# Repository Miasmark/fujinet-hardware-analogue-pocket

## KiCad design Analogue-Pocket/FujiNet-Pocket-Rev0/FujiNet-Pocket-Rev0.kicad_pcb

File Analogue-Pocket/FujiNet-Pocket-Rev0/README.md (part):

# FujiNet Pocket Rev0 (draft)

A **FujiNet for the Analogue Pocket's cartridge slot**. On the Pocket the FPGA core is the
cartridge:
- It serves the console's FujiNet mailbox to the running program.
- It sends each request as a FujiBus packet in a SLIP frame at 115,200 baud 8N1, on cartridge
  pin 5, and listens on pin 31.

This board is therefore only the FujiNet half of a FujiNet cartridge: no bus logic, no SRAM, no
console-side microcontroller. It is the same for every Pocket core that speaks this link. The
first is openFPGA-7800 (2.2.7: CONFIG, the network devices and game loading, tested with
fujinet-pc on the link port). An Intellivision core and a 2600 core are scoped to follow.
Cores of the cart's own, a net terminal and a text web browser, are scoped in
[docs/NET_CORES_SCOPING.md](docs/NET_CORES_SCOPING.md).

**Status (2026-11-20): draft, schematic and board.** It is placed and routed, but has not
been ordered, built or run, and has not been fitted to a Pocket.

| Check | Result |
|---|---|
| ERC (all severities) | 0 errors, 0 warnings |
| Netlist parity (kicad-cli netlist vs `tools/design.py`) | 41 / 41 nets |
| `tools/check_pins.py` (the netlist vs `firmware/pocket.h`, plus the link path) | pass |
| DRC, errors, with schematic parity | 0 violations, 0 unconnected, 0 parity |
| DRC warnings | 4: 2 dangling stitch vias, 2 silk near the edge |
| Shell, fit in a Pocket | draft shell drawn (`case/`), not yet printed or fitted |

`tools/build_all.sh` regenerates the schematic and the checks; `LAYOUT=1 tools/build_all.sh`
also regenerates the board and its outputs. It needs:
- KiCad 10 and Python 3;
- for the board, KiCad's pcbnew Python module (`PCBNEW_PYTHON`, default `/usr/bin/python3`) and
  numpy;
- Freerouting 2.4.1, which needs Java 25 (`JAVA` names the binary).
- The circuit lives in `tools/design.py`.
- The sheet drawings live in `tools/sch_layout.py`.
- The `.kicad_sch` files are output: edit the Python, not them.
- The generator, the drawing toolkit and its checks are FujiNet-7800-Rev0's (`ATARI-7800/`).

## Block diagram

```
Pocket slot ──pin 5──100R──[LVC1G34 on +3V3]──────── UART1 RX (IO17) ┐
            ──pin 31─100R──[LVC1G34 on CART_VCC]──── UART1 TX (IO18) ├ ESP32-S3-WROOM-1-N16R8 ── microSD
            ──pin 1 (CART_VCC) ─┐                                    │   UART0 ── CP2102N ── USB-C
                                └─ BAT54C ─ PWR_EN ─ TPS63001 (3.3 V)┘                         │
                                     VBUS ─┘           ▲ VSYS                                  │
                         LiPo ── AO3401A ──────────────┤                                       │
                          ▲                 SS34 ──────┘◄────────────── VBUS ◄────────────────┘
                          └── MCP73831 (4.20 V, 213 mA) ◄── VBUS
```

## The slot side (sheet 2)

The Pocket's slot is a GB / GBA edge: 32 fingers at 1.5 mm on one face.

| Pin | GBA / GB name | Net | Use |
|---|---|---|---|
| 1 | VCC | CART_VCC | The cart rail: 3.3 V while the Pocket runs with cart power on. The core asks for it (`core.json` `cartridge_adapter` 0). |
| 5 | /CS | POCKET_TX | The core's TX, idle high. |
| 31 | /REQ (GB: VIN) | POCKET_RX | The core's RX. |
| 32 | GND | GND | |
| others | | open | Analogue's template leaves them as they are: bank 0 an output held high, the rest inputs. |

- **Two SN74LVC1G34 buffers, both with Ioff** (partial power-down), so neither side ever feeds the
  other when it is off:
  - **RX buffer:** runs on the device's +3V3.
  - **TX buffer:** runs on the Pocket's own rail (pin 1).
  - The Pocket can be on with the device's cell flat, and the device can be on (charging, flashing)
  with the Pocket off.
- **100R in series at each finger.**
- **100k pull-downs** hold an unpowered side's line low:
  - The core counts a line only once it has idled high for 1 ms, so a low pin 31 is never heard.
  - The S3 sees a break, not noise.
- **Pin 1 also feeds the enable diode:** about 30 uA.

**Edge geometry** (`tools/make_edge_fp.py`) is re-drawn from Gekkio's GB-CART32K-A (gb-hardware,
CC-BY-4.0):
- pins 2-31 are 1.0 x 5.5 mm;
- pins 1 and 32 are 1.3 x 6.0 mm, so the rail and ground make contact first;
- the tab is 49.2 x 8.6 mm;
- the board is 1.0 mm thick.

**To verify on a Pocket before ordering boards:** which face the fingers are on, and pin 1.

## The FujiNet half (sheets 3 and 4)

FujiNet-7800-Rev0's circuits, unchanged except as noted:
- **ESP32-S3-WROOM-1-N16R8:** with its EN RC, S3_RST and S3_BOOT buttons, and 22 uF bulk.
- **microSD:** TF-015, SPI, with pull-ups.
- **USB-C:** HRO TYPE-C-31-M-12, 5.1k Rd, ESD.
- **CP2102N:** on UART0, with the UMH3N esptool auto-program pair.

Changed:
- **The link:** UART1 on IO17 (RX) and IO18 (TX) replaces the RP2354B's native USB and its
  RUN / BOOTSEL lines.
- **Status LEDs:** two plain LEDs, active low from +3V3, replace the WS2812C, which needs 3.7 V
  or more; this board has no 5 V rail.
  - WiFi: green, IO14.
  - Bus: red, IO16.

## Power (sheet 5)

The device powers itself. The Pocket's cart rail has only been seen to supply about 0.2 W. An
ESP32-S3 on WiFi averages more than that and peaks several times higher (openFPGA-7800
`docs/FUJINET_POCKET_DEVICE.md`, section 5).

- **Cell:** a protected 1S LiPo pouch up to 30 x 50 x 5 mm, for example a 403050 or 503050
  (about 600-1000 mAh). It rides over the components on a shelf in the shell (layout below), with
  its leads soldered to two pads on the board, marked + and -. There is no connector, so there is
  no JST-PH polarity to get wrong.
  - The board has no protection circuit of its own: the cell's is relied on.
  - The cell is bought separately and is not on the BOM.
- **Charger:** MCP73831-2 (4.20 V), 213 mA (R_PROG 4.7k, about 0.5 C for 400 mAh), from USB
  only, with a charge LED.
- **Power path** (Microchip AN1149, as the 7800 board's 5 V OR):
  - USB VBUS goes through an SS34 onto VSYS.
  - The cell goes through an AO3401A, gate on VBUS: on without USB, off with it, so USB runs the
    board while the cell charges.
  - 4.7k holds the gate down against the SS34's leakage.
- **3.3 V:** a TPS63001 buck-boost, 1.8-5.5 V in. It holds 3.3 V over the cell's whole 3.0-4.2 V
  and through WiFi bursts.
  - PS/SYNC is tied low: power-save mode at light load.
- **Enable:** `PWR_EN = CART_VCC or VBUS` (BAT54C, 100k down).
  - The board runs while the Pocket is on, or while USB is in (charging, flashing).
  - Otherwise the regulator is shut down: no power switch is needed.

## Firmware

`firmware/pocket.h` and `firmware/platformio-fujinet-pocket.ini` are proposed for fujinet-firmware
as `include/pinmap/pocket.h` and `build-platforms/platformio-fujinet-pocket.ini`:
- **The build:** the generic RS232 build (`BUILD_RS232`) on a wired UART, as `rs232_s3.h`.
- **Pin assignments:**
  - **UART1:** the link, on 17 and 18. Defining `PIN_UART1_RX` is what selects the wired UART in
    `lib/bus/rs232/rs232.h`.
  - **SD and UART0:** as `fujiversal-rs232.h`.
  - **LEDs:** on 14 and 16.
  - **Not used:** the modem control lines and keys.cpp's buttons are `GPIO_NUM_NC`.
    `common.h` would otherwise put button C on GPIO14, this board's WiFi LED.

`pinmap.h` also needs its `#include "pinmap/pocket.h"`. Neither file has been compiled yet.

**It is also a modem.** The stock RS232 firmware passes any bytes outside
FujiBus frames to FujiNet's Hayes-style modem: a terminal core on the cart's
pins (NetTerm, Mode FujiNet Modem) dials Telnet BBSs with `ATDT host:port`.
See `docs/NET_CORES_SCOPING.md`, section 2.
## The board

- **Size and stack:** 51.4 x 82 mm, 1.0 mm thick, 4 layers:
  - F.Cu: signals and a GND pour;
  - In1: GND plane;
  - In2: +3V3 plane;
  - B.Cu: signals and a GND pour.
- **The tab:** the GB / GBA tab with its 32 fingers. The insertion corners are 0.9 mm arcs, as a
  GB cartridge's.
- **The voltage-switch corner:** on the left (pin 1's side, seen from the component side with
  the fingers down), the tab's edge runs straight on up 10 mm past the tab base before the body
  steps out to full width. The shell's GBA-shaped corner there then clears the Pocket's voltage
  switch. The height is an **estimate** (`gen_pcb.NOTCH_H`).
- **The Pocket's cartridge recess** (estimates, both drawn on the board's Fab layers):
  - **Back:** below about 31 mm from the insertion edge, the board's flat back lies nearly flush
    against the Pocket. Nothing is placed on the back.
  - **Front** (the component side, the fingers' side): it faces the recess's open side, covered
    only by the Pocket's lip below about 15 mm from the insertion edge. Only low parts go there:
    the two link buffers over pins 5 and 31, the bring-up pads, the cell's lead pads.
- **Above the recess, on the front:**
  - the ESP32-S3 at the top, its antenna flush with the top edge over its keep-out band (no
    copper, holes or parts across the board there);
  - USB-C on the west side and microSD on the east side;
  - the reset and BOOT buttons and the three LEDs down the west side;
  - below the module: the charger and power path, the TPS63001, the CP2102N.
- **The battery, on a shelf in the shell:**
  - the cell lies over the components, on a shelf whose top face is 4.4 mm above the board. The
    tallest parts under it are the module and USB-C, at 3.1-3.2 mm.
  - its place, 30 x 50 mm (x 88..118, y 79..129), is drawn on F.Fab and in the shell anchors. It
    is clear of the antenna band and the two buttons.
  - its leads come down from its lower end to two pads on the component side, just above the lip:
    `+` at the east, `-` at the west.
  - the 3D export shows a 30 x 50 x 4 mm stand-in at that height.
  - nothing is placed on the back, so assembly is single-sided.
- **Six M2 holes** (2.2 mm) for the shell, each kept 3 mm clear of parts:
  - two by the top corners, below the antenna band;
  - two just above the slot line;
  - two inside the slot.

  `case/board-anchors.json` and `.scad` carry them for the shell design, with the outline, the
  ports, buttons, LEDs and the cell. `case/README.md` lists what the shell must respect: the
  GBA-shaped corner, the antenna, the openings and the cell's room to swell.
- **Routing:** generated, as for FujiNet-7800-Rev0. The order:
  1. `tools/gen_pcb.py` places the parts from `tools/placement.py` and fans out the planes. It also
     lays four things down by hand, locked:
     - the TPS63001's pins, to its inductor and capacitors as its datasheet shows, and its VIN /
       VINA loop;
     - the USB pair: the USB-C crossover (D- under it on B.Cu, through two 0.45 / 0.2 mm vias),
       on to the ESD diodes, then on B.Cu under the SS34 and the power path to the CP2102N's
       pins 4 and 5;
     - the UART0 escapes from the module to B.Cu;
     - the GND finger's stub.
  2. Freerouting routes the rest.
  3. The 7800 board's finisher closes what is left; stitching vias tie the GND pours to In1.
- **Outputs** (`tools/export_fab.py`): `exports/`
  - gerbers and drill;
  - the front position file;
  - `FujiNet-Pocket-Rev0.step` (the board with every model and the cell's stand-in, for the
    shell);
  - the renders in `docs/`.

## Measure with the breakout cart

These numbers are estimates in the board and shell; each is one setting in `tools/gen_pcb.py`
(and `tools/placement.py` for the slot line), then `LAYOUT=1 tools/build_all.sh` re-runs the
layout and the shell anchors.

| # | Measure | Now (estimate) | Setting |
|---|---|---|---|
| 1 | **Voltage switch:** how far above the tab base the left corner must stay at the tab's width | 10 mm | `NOTCH_H` |
| 2 | **Seated depth:** how far from the insertion edge the board's back starts lying against the Pocket | 31 mm (y = 119) | `SLOT_Y` (gen_pcb.py and placement.py) |
| 3 | **Lip:** how far up the component side the Pocket's lip covers (low parts only below) | 15 mm (y = 135) | `LIP_Y` (gen_pcb.py and placement.py) |
| 4 | **Board thickness** the slot wants | 1.0 mm (Gekkio's GB boards) | `THICKNESS` |
| 5 | **Pin 1 side:** VCC (pin 1) on the left, seen from the contact side with the fingers down | as Gekkio's footprint | `make_edge_fp.py` |

**Final pass, after the measurements and the re-route:** clear the DRC warnings left then.
Today these are 2 dangling stitching vias and 2 silkscreen texts near the edge. Re-check the
renders and the shell anchors, and fit a printed blank.

## Before ordering boards

1. **Edge:** check the finger face, pin 1 and the board thickness (1.0 mm, as Gekkio's GB
   boards) against a GB cartridge in a Pocket. Measure where the Pocket's shell top falls on the
   board (31 mm from the insertion edge is assumed), and how far up the component side the
   Pocket's lip covers it (15 mm is assumed: only low parts below). Measure the voltage switch
   and size the left corner's step for it (10 mm above the tab base is assumed).
2. **Shell:** print a blank with the GBA-shaped corner first, and check that it seats fully and
   clears the voltage switch and the shoulder buttons (`case/README.md`).
3. **Sourcing:** no LCSC code chosen yet for SN74LVC1G34DBVR, MCP73831T-2ACI/OT, TPS63001DRCR,
   SWPA4030S1R5NT and the green LED (`FujiNet-Pocket-Rev0-BOM.csv`).
4. **The inductor's saturation current** against the TPS63001's switch current limit (datasheet).
5. **The microSD card-detect polarity:** it is wired to IO42 and set NC in `pocket.h` until known.
6. **The back in the recess:** check that the board's back, with its tented vias and silk,
   slides against the Pocket without catching. The USB-C's shell legs and the microSD's pegs come
   through it above the recess.
7. **Fab review:**
   - the 4-layer, 1.0 mm stack;
   - hard gold on the fingers, with a bevel;
   - the 0.45 / 0.2 mm vias;
   - JLCPCB's placement preview (no CPL rotation corrections are made for this board yet).
8. **Compile `pocket.h`** in fujinet-firmware; offer the pin map upstream once a board has run.
9. **Silkscreen:** the link to github.com/FujiNetWIFI is on the back, as this repository's notice
   requires.

## Files

| Path | What |
|---|---|
| `tools/design.py` | The circuit: every part, value, footprint, MPN, LCSC code and net. |
| `tools/sch_layout.py` | How each sheet is drawn. |
| `tools/gen_sch.py`, `sch_draw.py`, `sexpr.py` | The generator and its checks (FujiNet-7800-Rev0's). |
| `tools/harvest_symbols.py`, `symcache.sexpr` | The stock symbols embedded in the sheets. |
| `tools/make_edge_fp.py` | The slot edge footprint. |
| `tools/make_fp_extra.py` | The cell's lead pads footprint. |
| `tools/make_cell_step.py` | The cell's stand-in 3D model (a 30 x 50 x 4 mm box at shelf height, STEP written by hand). |
| `tools/placement.py`, `tools/gen_pcb.py` | Where every part goes; the board generator (outline, holes, planes, keep-outs, the pre-routes, the shell anchors). |
| `tools/fanout.py`, `route.py`, `finish_route.py`, `drc_fix.py`, `tidy_tracks.py`, `stitch_gnd.py`, `check_vias.py`, `fix_silk.py`, `fill_zones.py`, `set_models.py`, `route_board.sh` | Plane fan-out, Freerouting, the finisher and clean-up (FujiNet-7800-Rev0's). |
| `tools/export_fab.py` | Gerbers, drill, positions, STEP, renders. |
| `FujiNet-Pocket-Rev0.kicad_pcb` | The board (generated). |
| `case/` | The draft shell (`FujiNet-Pocket-Shell.scad`, STLs in `case/stl/`), its notes, and the board's anchors for it. |
| `3d/` | The 3D models (FujiNet-7800-Rev0's set, plus the cell's stand-in). |
| `exports/` | The fab and STEP outputs. |
| `tools/check_pins.py` | The netlist against `firmware/pocket.h` and the link path. |
| `tools/bom.py` | `FujiNet-Pocket-Rev0-BOM.csv`. |
| `firmware/` | The proposed fujinet-firmware pin map and build env. |
| `docs/FujiNet-Pocket-Rev0-schematic.pdf` | The schematic. |
| `docs/NET_CORES_SCOPING.md` | Scoping note: other cores for the cart (a net terminal, a text web browser) and why an "update cores" core isn't possible today. |

## Provenance and license

**CERN-OHL-W-2.0**, as FujiNet-7800-Rev0.
- **The FujiNet half, the generators and the drawing toolkit:** `ATARI-7800/FujiNet-7800-Rev0` in
  this repository, and through it SMS / NES Rev0.
- **The slot side, the LEDs and the power sheet:** new.
- **Edge geometry:** Gekkio, gb-hardware GB-CART32K-A, CC-BY-4.0 (measurements re-drawn).
- **The link protocol and pins:** openFPGA-7800 (MIT), `docs/FUJINET_POCKET_DEVICE.md`,
  `src/fpga/core/fujinet_mailbox.sv`.
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
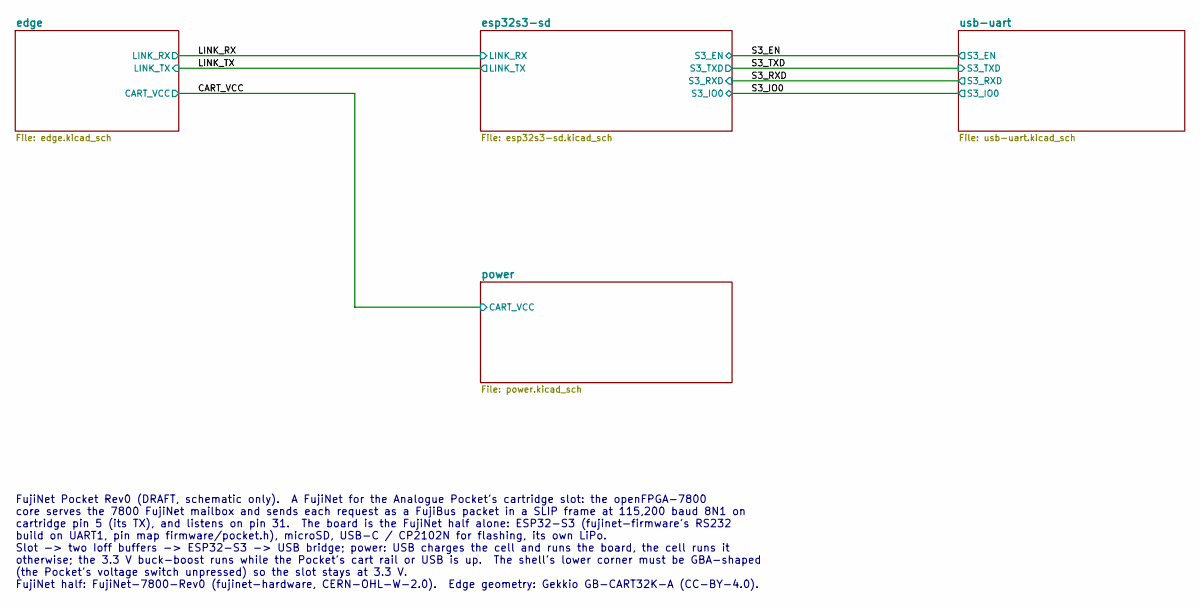
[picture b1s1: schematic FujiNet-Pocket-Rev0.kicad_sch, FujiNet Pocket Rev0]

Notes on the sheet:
FujiNet Pocket Rev0 (DRAFT, schematic only). A FujiNet for the Analogue Pocket's cartridge slot: the openFPGA-7800 core serves the 7800 FujiNet mailbox and sends each request as a FujiBus packet in a SLIP frame at 115,200 baud 8N1 on cartridge pin 5 (its TX), and listens on pin 31. The board is the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

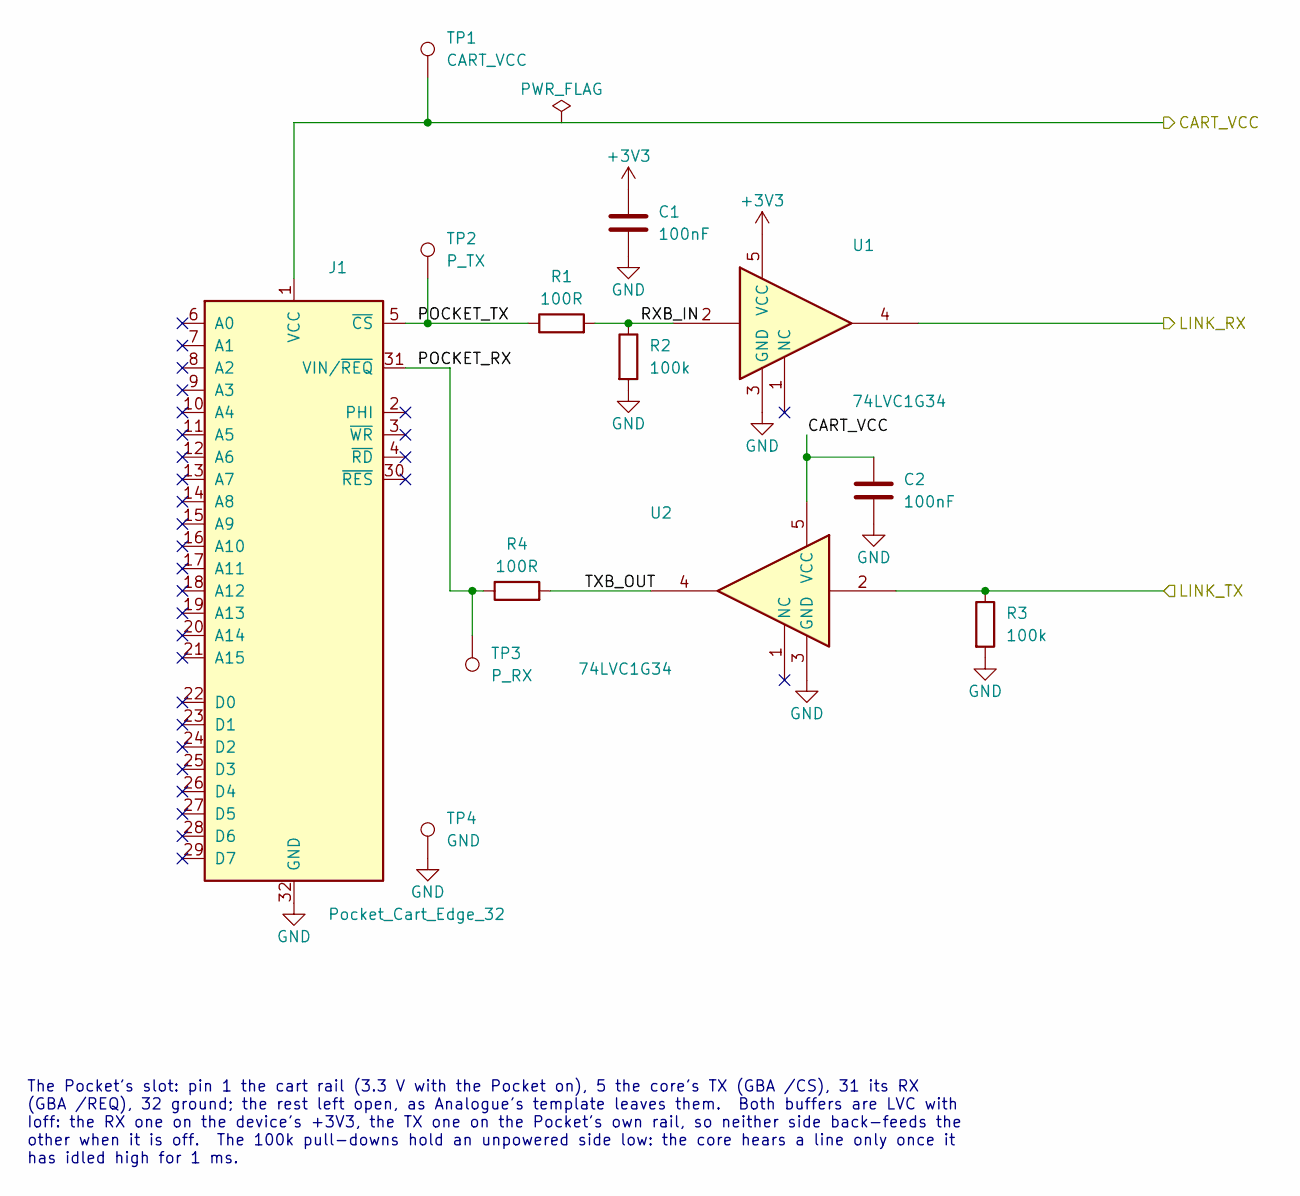
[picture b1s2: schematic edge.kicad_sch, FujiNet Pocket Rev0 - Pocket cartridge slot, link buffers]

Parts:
C1, C2: 100nF; C_0603_1608Metric; MPN CC0603KRX7R9BB104; LCSC C14663
J1: Pocket_Cart_Edge_32
R1, R4: 100R; R_0603_1608Metric; MPN 0603WAF1000T5E; LCSC C22775
R2, R3: 100k; R_0603_1608Metric; MPN 0603WAF1003T5E; LCSC C25803
TP1: CART_VCC; TestPoint_Pad_D1.5mm
TP2: P_TX; TestPoint_Pad_D1.5mm
TP3: P_RX; TestPoint_Pad_D1.5mm
TP4: GND; TestPoint_Pad_D1.5mm
U1, U2: 74LVC1G34; SOT-23-5; MPN SN74LVC1G34DBVR

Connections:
+3V3: C1.1, U1.5 (VCC); also elsewhere on the board
/CART_VCC: C2.1, J1.1 (VCC), TP1.1, U2.5 (VCC); also elsewhere on the board
/LINK_RX: U1.4; also elsewhere on the board
/LINK_TX: R3.1, U2.2; also elsewhere on the board
/edge/POCKET_RX: J1.31 (VIN/~REQ), R4.1, TP3.1
/edge/POCKET_TX: J1.5 (~CS), R1.1, TP2.1
/edge/RXB_IN: R1.2, R2.1, U1.2
/edge/TXB_OUT: R4.2, U2.4
GND: C1.2, C2.2, J1.32 (GND), R2.2, R3.2, TP4.1, U1.3 (GND), U2.3 (GND); also elsewhere on the board

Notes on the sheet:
The Pocket's slot: pin 1 the cart rail (3.3 V with the Pocket on), 5 the core's TX (GBA /CS), 31 its RX (GBA /REQ), 32 ground; the rest left open, as Analogue's template leaves them. Both buffers are LVC with Ioff: the RX one on the device's +3V3, the TX one on the Pocket's own rail, so neither sid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

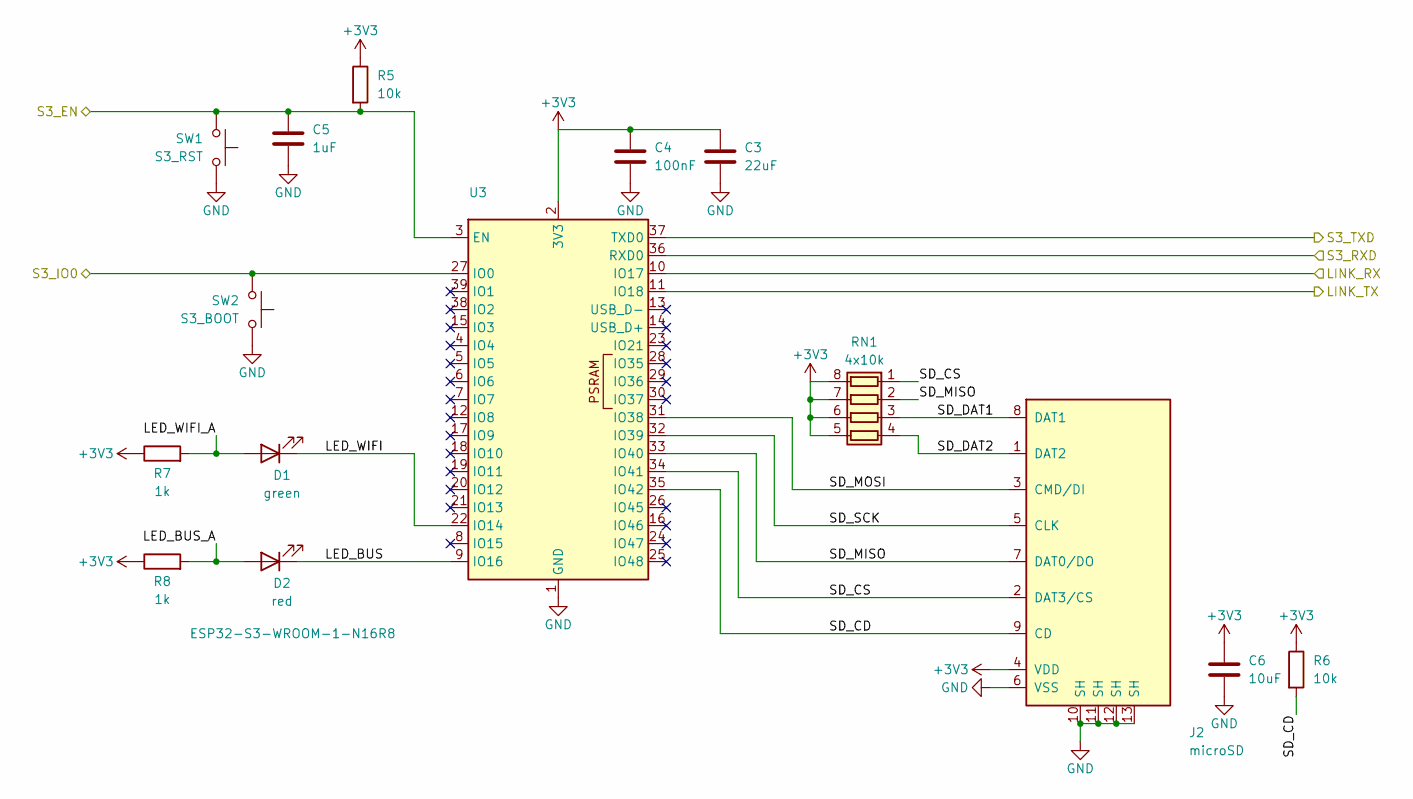
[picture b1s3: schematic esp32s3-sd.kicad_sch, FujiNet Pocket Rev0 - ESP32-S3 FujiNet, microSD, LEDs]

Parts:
C3: 22uF; C_0805_2012Metric; MPN CL21A226MAQNNNE; LCSC C45783
C4: 100nF; C_0603_1608Metric; MPN CC0603KRX7R9BB104; LCSC C14663
C5: 1uF; C_0603_1608Metric; MPN CL10A105KB8NNNC; LCSC C15849
C6: 10uF; C_0603_1608Metric; MPN CL10A106KP8NNNC; LCSC C19702
D1: green; LED_0603_1608Metric; MPN KT-0603G
D2: red; LED_0603_1608Metric; MPN KT-0603R; LCSC C2286
J2: microSD; TF-SMD_TF-015; MPN TF-015; LCSC C113206
R5, R6: 10k; R_0603_1608Metric; MPN 0603WAF1002T5E; LCSC C25804
R7, R8: 1k; R_0603_1608Metric; MPN 0603WAF1001T5E; LCSC C21190
RN1: 4x10k; R_Array_Convex_4x0603; MPN 4D03WGJ0103T5E; LCSC C29718
SW1: S3_RST; SW_SPST_TS-1187A; MPN TS-1187A-B-A-B; LCSC C318884
SW2: S3_BOOT; SW_SPST_TS-1187A; MPN TS-1187A-B-A-B; LCSC C318884
U3: ESP32-S3-WROOM-1-N16R8; ESP32-S3-WROOM-1; MPN ESP32-S3-WROOM-1-N16R8; LCSC C2913202

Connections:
+3V3: C3.1, C4.1, C6.1, J2.4 (VDD), R5.1, R6.1, R7.1, R8.1, RN1.5 (R4.2), RN1.6 (R3.2), RN1.7 (R2.2), RN1.8 (R1.2), U3.2 (3V3); also elsewhere on the board
/LINK_RX: U3.10 (IO17); also elsewhere on the board
/LINK_TX: U3.11 (IO18); also elsewhere on the board
/S3_EN: C5.1, R5.2, SW1.1, U3.3 (EN); also elsewhere on the board
/S3_IO0: SW2.1, U3.27 (IO0); also elsewhere on the board
/S3_RXD: U3.36 (RXD0); also elsewhere on the board
/S3_TXD: U3.37 (TXD0); also elsewhere on the board
/esp32s3-sd/LED_BUS: D2.1 (K), U3.9 (IO16)
/esp32s3-sd/LED_BUS_A: D2.2 (A), R8.2
/esp32s3-sd/LED_WIFI: D1.1 (K), U3.22 (IO14)
/esp32s3-sd/LED_WIFI_A: D1.2 (A), R7.2
/esp32s3-sd/SD_CD: J2.9 (CD), R6.2, U3.35 (IO42)
/esp32s3-sd/SD_CS: J2.2 (DAT3/CS), RN1.1 (R1.1), U3.34 (IO41)
/esp32s3-sd/SD_DAT1: J2.8 (DAT1), RN1.3 (R3.1)
/esp32s3-sd/SD_DAT2: J2.1 (DAT2), RN1.4 (R4.1)
/esp32s3-sd/SD_MISO: J2.7 (DAT0/DO), RN1.2 (R2.1), U3.33 (IO40)
/esp32s3-sd/SD_MOSI: J2.3 (CMD/DI), U3.31 (IO38)
/esp32s3-sd/SD_SCK: J2.5 (CLK), U3.32 (IO39)
GND: C3.2, C4.2, C5.2, C6.2, J2.6 (VSS), J2.10 (SH), J2.11 (SH), J2.12 (SH), J2.13 (SH), SW1.2, SW2.2, U3.1 (GND), U3.40 (GND), U3.41 (GND); also elsewhere on the board

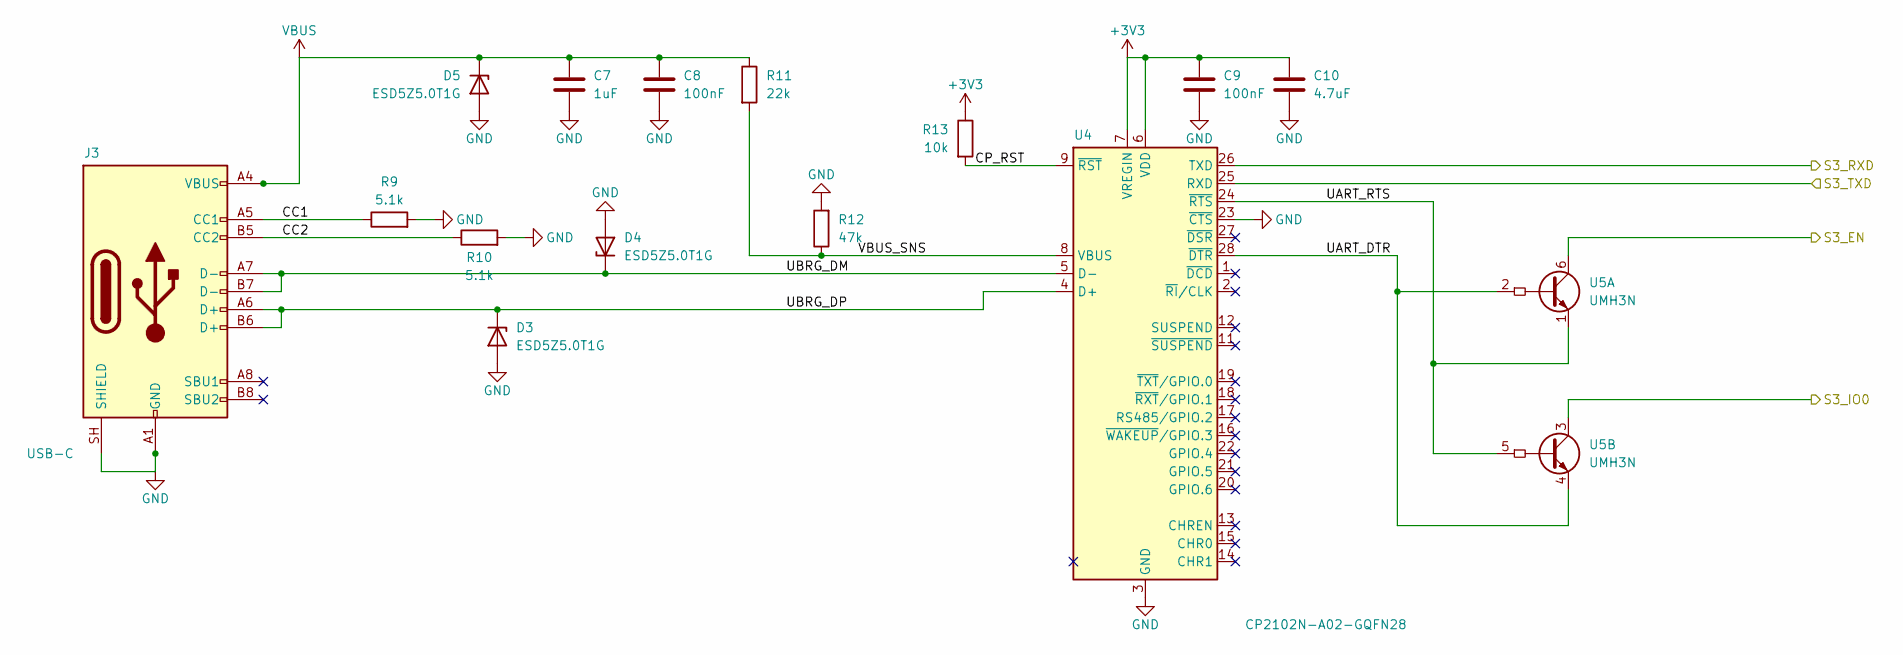
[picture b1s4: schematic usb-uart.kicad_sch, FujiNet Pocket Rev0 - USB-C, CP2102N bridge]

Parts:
C7: 1uF; C_0603_1608Metric; MPN CL10A105KB8NNNC; LCSC C15849
C8, C9: 100nF; C_0603_1608Metric; MPN CC0603KRX7R9BB104; LCSC C14663
C10: 4.7uF; C_0603_1608Metric; MPN CL10A475KO8NNNC; LCSC C19666
D3, D4, D5: ESD5Z5.0T1G; D_SOD-523; MPN ESD5Z5.0T1G; LCSC C82044
J3: USB-C; USB_C_Receptacle_HRO_TYPE-C-31-M-12; MPN TYPE-C-31-M-12; LCSC C165948
R9, R10: 5.1k; R_0603_1608Metric; MPN 0603WAF5101T5E; LCSC C23186
R11: 22k; R_0603_1608Metric; MPN 0603WAF2202T5E; LCSC C31850
R12: 47k; R_0603_1608Metric; MPN 0603WAF4702T5E; LCSC C25819
R13: 10k; R_0603_1608Metric; MPN 0603WAF1002T5E; LCSC C25804
U4: CP2102N-A02-GQFN28; QFN-28-1EP_5x5mm_P0.5mm_EP3.35x3.35mm; MPN CP2102N-A02-GQFN28R; LCSC C964632
U5: UMH3N; SOT-363_SC-70-6; MPN UMH3N; LCSC C62892

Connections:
+3V3: C9.1, C10.1, R13.1, U4.6 (VDD), U4.7 (VREGIN); also elsewhere on the board
/S3_EN: U5.6 (C1); also elsewhere on the board
/S3_IO0: U5.3 (C2); also elsewhere on the board
/S3_RXD: U4.26 (TXD); also elsewhere on the board
/S3_TXD: U4.25 (RXD); also elsewhere on the board
/usb-uart/CC1: J3.A5 (CC1), R9.1
/usb-uart/CC2: J3.B5 (CC2), R10.1
/usb-uart/CP_RST: R13.2, U4.9 (~RST)
/usb-uart/UART_DTR: U4.28 (~DTR), U5.2 (B1), U5.4 (E2)
/usb-uart/UART_RTS: U4.24 (~RTS), U5.1 (E1), U5.5 (B2)
/usb-uart/UBRG_DM: D4.1 (K), J3.A7 (D-), J3.B7 (D-), U4.5 (D-)
/usb-uart/UBRG_DP: D3.1 (K), J3.A6 (D+), J3.B6 (D+), U4.4 (D+)
/usb-uart/VBUS_SNS: R11.2, R12.1, U4.8 (VBUS)
GND: C7.2, C8.2, C9.2, C10.2, D3.2 (A), D4.2 (A), D5.2 (A), J3.A1 (GND), J3.A12 (GND), J3.B1 (GND), J3.B12 (GND), J3.SH (SHIELD), R9.2, R10.2, R12.2, U4.3 (GND), U4.23 (~CTS), U4.29 (GND); also elsewhere on the board
VBUS: C7.1, C8.1, D5.1 (K), J3.A4 (VBUS), J3.A9 (VBUS), J3.B4 (VBUS), J3.B9 (VBUS), R11.1; also elsewhere on the board

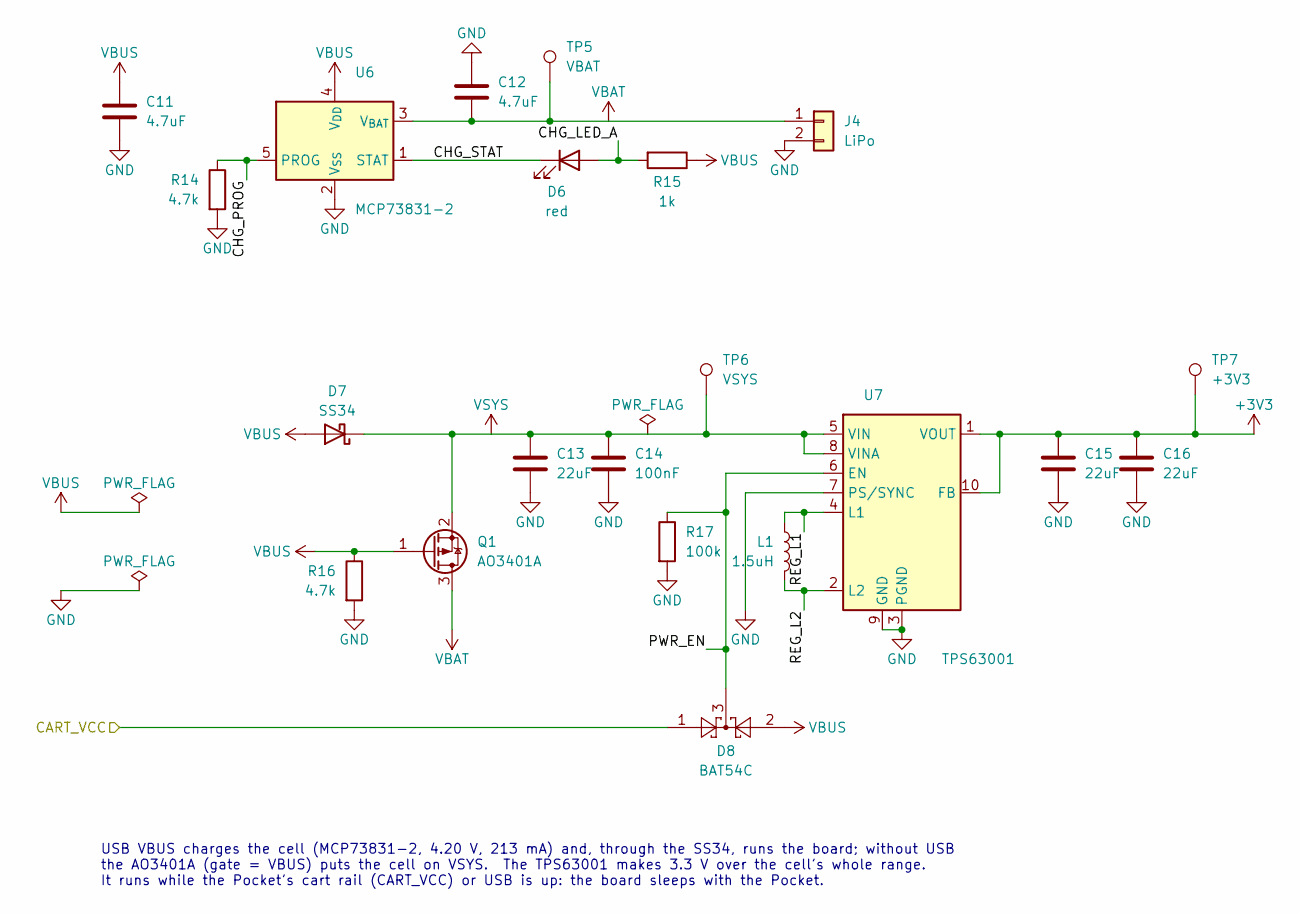
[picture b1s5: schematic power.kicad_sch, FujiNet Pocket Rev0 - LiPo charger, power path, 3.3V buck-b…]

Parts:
C11, C12: 4.7uF; C_0603_1608Metric; MPN CL10A475KO8NNNC; LCSC C19666
C13, C15, C16: 22uF; C_0805_2012Metric; MPN CL21A226MAQNNNE; LCSC C45783
C14: 100nF; C_0603_1608Metric; MPN CC0603KRX7R9BB104; LCSC C14663
D6: red; LED_0603_1608Metric; MPN KT-0603R; LCSC C2286
D7: SS34; D_SMA; MPN SS34; LCSC C8678
D8: BAT54C; SOT-23; MPN BAT54C,215; LCSC C37704
J4: LiPo; LiPo_Leads
L1: 1.5uH; L_Sunlord_SWPA4030S; MPN SWPA4030S1R5NT
Q1: AO3401A; SOT-23; MPN AO3401A; LCSC C15127
R14, R16: 4.7k; R_0603_1608Metric; MPN 0603WAF4701T5E; LCSC C23162
R15: 1k; R_0603_1608Metric; MPN 0603WAF1001T5E; LCSC C21190
R17: 100k; R_0603_1608Metric; MPN 0603WAF1003T5E; LCSC C25803
TP5: VBAT; TestPoint_Pad_D1.5mm
TP6: VSYS; TestPoint_Pad_D1.5mm
TP7: +3V3; TestPoint_Pad_D1.5mm
U6: MCP73831-2; SOT-23-5; MPN MCP73831T-2ACI/OT
U7: TPS63001; Texas_DRC0010J; MPN TPS63001DRCR

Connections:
+3V3: C15.1, C16.1, TP7.1, U7.1 (VOUT), U7.10 (FB); also elsewhere on the board
/CART_VCC: D8.1; also elsewhere on the board
/power/CHG_LED_A: D6.2 (A), R15.2
/power/CHG_PROG: R14.1, U6.5 (PROG)
/power/CHG_STAT: D6.1 (K), U6.1 (STAT)
/power/PWR_EN: D8.3, R17.1, U7.6 (EN)
/power/REG_L1: L1.1, U7.4 (L1)
/power/REG_L2: L1.2, U7.2 (L2)
GND: C11.2, C12.2, C13.2, C14.2, C15.2, C16.2, J4.2, R14.2, R16.2, R17.2, U6.2 (V_{SS}), U7.3 (PGND), U7.7 (PS/SYNC), U7.9 (GND), U7.11 (PGND); also elsewhere on the board
VBAT: C12.1, J4.1, Q1.3 (D), TP5.1, U6.3 (V_{BAT})
VBUS: C11.1, D7.2 (A), D8.2, Q1.1 (G), R15.1, R16.1, U6.4 (V_{DD}); also elsewhere on the board
VSYS: C13.1, C14.1, D7.1 (K), Q1.2 (S), TP6.1, U7.5 (VIN), U7.8 (VINA)

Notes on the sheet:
USB VBUS charges the cell (MCP73831-2, 4.20 V, 213 mA) and, through the SS34, runs the board; without USB the AO3401A (gate = VBUS) puts the cell on VSYS. The TPS63001 makes 3.3 V over the cell's whole range. It runs while the Pocket's cart rail (CART_VCC) or USB is up: the board sleeps with the Po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

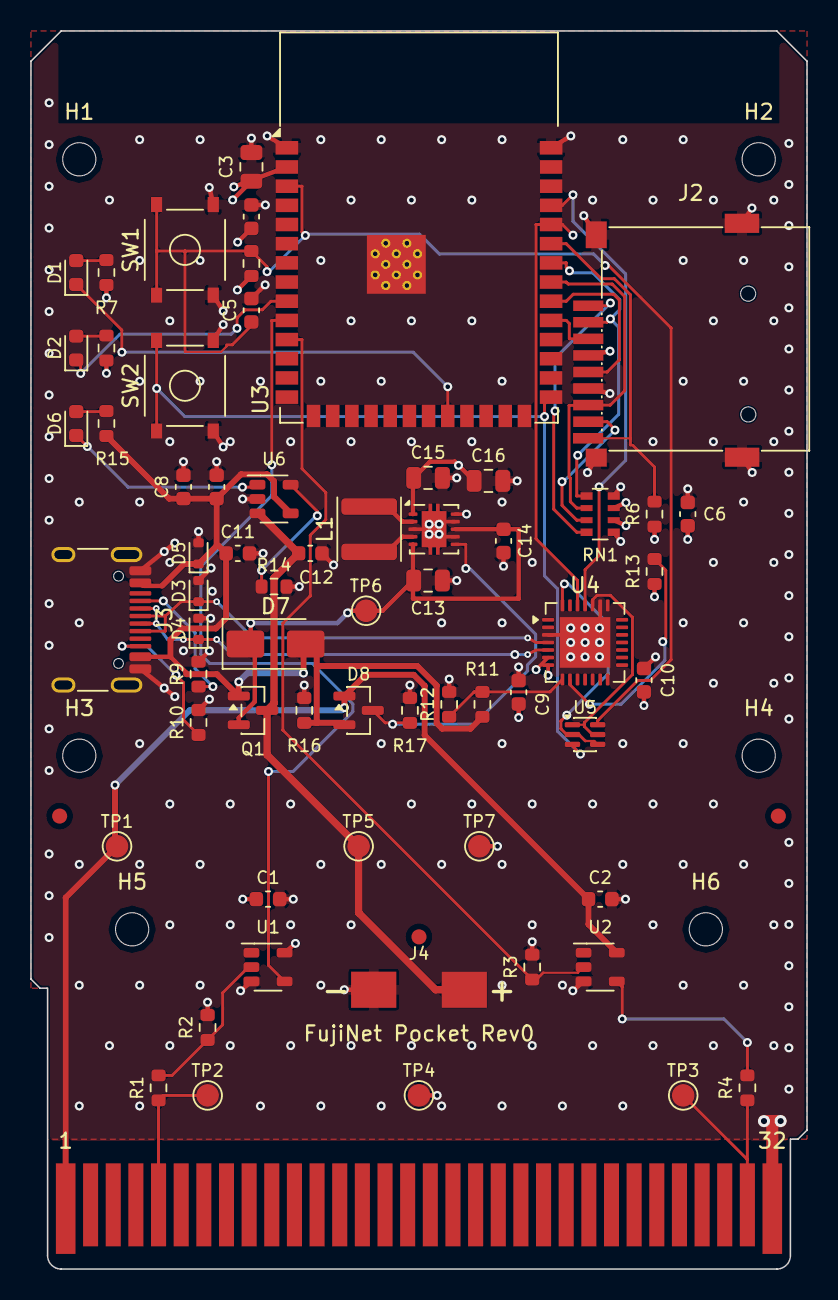
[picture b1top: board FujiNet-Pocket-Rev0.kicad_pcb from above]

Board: 4 copper layers, 51.4 x 82.0 mm, 73 parts (0 on the bottom side), 41 nets.

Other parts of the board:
FID1, FID2, FID3: Fiducial_1mm_Mask2mm
H1, H2, H3, H4, H5, H6: MountingHole_2.2mm_M2

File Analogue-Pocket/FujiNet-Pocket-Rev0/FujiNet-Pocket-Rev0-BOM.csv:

References,Qty,Value,Footprint,Manufacturer,MPN,LCSC,DNP,Description
C1 C2 C4 C8 C9 C14,6,100nF,C_0603_1608Metric,YAGEO,CC0603KRX7R9BB104,C14663,,RX buffer VCC
C3 C13 C15 C16,4,22uF,C_0805_2012Metric,Samsung Electro-Mechanics,CL21A226MAQNNNE,C45783,,S3 bulk (WiFi TX bursts)
C5 C7,2,1uF,C_0603_1608Metric,Samsung Electro-Mechanics,CL10A105KB8NNNC,C15849,,EN power-on delay
C6,1,10uF,C_0603_1608Metric,Samsung Electro-Mechanics,CL10A106KP8NNNC,C19702,,microSD supply
C10 C11 C12,3,4.7uF,C_0603_1608Metric,Samsung Electro-Mechanics,CL10A475KO8NNNC,C19666,,CP2102N VDD bulk
D1,1,green,LED_0603_1608Metric,Hubei KENTO Elec,KT-0603G,,,"WiFi LED (IO14, low = on)"
D2 D6,2,red,LED_0603_1608Metric,Hubei KENTO Elec,KT-0603R,C2286,,"bus activity LED (IO16, low = on)"
D3 D4 D5,3,ESD5Z5.0T1G,D_SOD-523,onsemi,ESD5Z5.0T1G,C82044,,ESD
D7,1,SS34,D_SMA,MDD (Microdiode Semiconductor),SS34,C8678,,USB VBUS onto VSYS
D8,1,BAT54C,SOT-23,Nexperia,"BAT54C,215",C37704,,"PWR_EN = CART_VCC or VBUS, common cathode"
J2,1,microSD,TF-SMD_TF-015,SOFNG,TF-015,C113206,,"microSD push-push, SPI mode"
J3,1,USB-C,USB_C_Receptacle_HRO_TYPE-C-31-M-12,Korean Hroparts Elec,TYPE-C-31-M-12,C165948,,charging + S3 programming
L1,1,1.5uH,L_Sunlord_SWPA4030S,Sunlord,SWPA4030S1R5NT,,,buck-boost inductor (datasheet: 1.5 uH)
Q1,1,AO3401A,SOT-23,Alpha & Omega Semiconductor,AO3401A,C15127,,"cell onto VSYS without USB: G = VBUS, S = VSYS, D = VBAT"
R1 R4,2,100R,R_0603_1608Metric,UNI-ROYAL,0603WAF1000T5E,C22775,,link RX: series at the finger
R2 R3 R17,3,100k,R_0603_1608Metric,UNI-ROYAL,0603WAF1003T5E,C25803,,link RX: defined low with the Pocket off
R5 R6 R13,3,10k,R_0603_1608Metric,UNI-ROYAL,0603WAF1002T5E,C25804,,EN pull-up
R7 R8 R15,3,1k,R_0603_1608Metric,UNI-ROYAL,0603WAF1001T5E,C21190,,WiFi LED series
R9 R10,2,5.1k,R_0603_1608Metric,UNI-ROYAL,0603WAF5101T5E,C23186,,UFP Rd
R11,1,22k,R_0603_1608Metric,UNI-ROYAL,0603WAF2202T5E,C31850,,VBUS sense divider
R12,1,47k,R_0603_1608Metric,UNI-ROYAL,0603WAF4702T5E,C25819,,VBUS sense divider
R14 R16,2,4.7k,R_0603_1608Metric,UNI-ROYAL,0603WAF4701T5E,C23162,,charge current 213 mA (1000 V / R)
RN1,1,4x10k,R_Array_Convex_4x0603,UNI-ROYAL,4D03WGJ0103T5E,C29718,,SD pull-ups
SW1,1,S3_RST,SW_SPST_TS-1187A,XKB Connection,TS-1187A-B-A-B,C318884,,ESP32-S3 EN (reset)
SW2,1,S3_BOOT,SW_SPST_TS-1187A,XKB Connection,TS-1187A-B-A-B,C318884,,ESP32-S3 BOOT (IO0)
U1 U2,2,74LVC1G34,SOT-23-5,Texas Instruments,SN74LVC1G34DBVR,,,link RX buffer on +3V3 (Pocket TX -> S3 UART1 RX)
U3,1,ESP32-S3-WROOM-1-N16R8,ESP32-S3-WROOM-1,Espressif,ESP32-S3-WROOM-1-N16R8,C2913202,,"FujiNet core (RS232 build, pocket pin map)"
U4,1,CP2102N-A02-GQFN28,QFN-28-1EP_5x5mm_P0.5mm_EP3.35x3.35mm,Silicon Labs,CP2102N-A02-GQFN28R,C964632,,USB-UART for S3 flashing/console (self-powered)
U5,1,UMH3N,SOT-363_SC-70-6,Jiangsu Changjing (JSCJ),UMH3N,C62892,,esptool auto-program (DevKitC-1 style)
U6,1,MCP73831-2,SOT-23-5,Microchip,MCP73831T-2ACI/OT,,,"1S LiPo charger, 4.20 V, from USB only"
U7,1,TPS63001,Texas_DRC0010J,Texas Instruments,TPS63001DRCR,,,"3.3 V buck-boost, 1.2 A (buck) / 800 mA from 2.4 V (boost)"

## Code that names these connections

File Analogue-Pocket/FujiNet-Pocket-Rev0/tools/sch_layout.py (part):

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    """The Pocket's slot on the left, everything but its rail, ground and two link pins left open.
    Pin 5 (the core's TX) comes in through 100R into the RX buffer on the device's +3V3 and leaves
    as LINK_RX; LINK_TX from the S3 goes out through the TX buffer, powered from the slot's own
    rail, and 100R to pin 31 (the core's RX).  The rail (pin 1) leaves as CART_VCC for the power
    sheet's enable."""
    J = 'J_EDGE'
    X, Y = 60.96, 104.14
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    ncs(sh, J)
    col = 160.02
    sh.gnd(sh.P(J, 32))
    # CART_VCC: pin 1 up and out along the top, a bring-up pad and the PWR_FLAG on it
    v = sh.P(J, 1)
    ty = 50.8
    sh.wire(v, (v[0], ty), (91.44, ty), (col, ty))
    sh.hlabel(Pt(col, ty), 'CART_VCC', 'R', 'output')
    tap_tp(sh, 'TP_CVCC', (76.2, ty))
    sh.flag((91.44, ty), 'CART_VCC')
    sh.place('TP_GNDE', 76.2, 134.62, fields='right')
    sh.gnd(sh.P('TP_GNDE', 1))
    # RX: pin 5 -> 100R -> (100k down) -> buffer on +3V3 -> LINK_RX
    p = sh.P(J, 5)
    ry = p[1]
    tap_tp(sh, 'TP_PTX', (76.2, ry))
    sh.place('R_RXIN', 91.44, ry, rot=90, fields='above')
    sh.wire(p, sh.N('R_RXIN', 'POCKET_TX'))
    sh.label((p[0] + 1.27, ry), 'POCKET_TX')
    sh.place('R_RXPD', 99.06, ry + 3.81, fields='right')
    sh.gnd(sh.P('R_RXPD', 2))
    B = 'U_RXBUF'
    sh.place(B, 119.38, ry, fields='abovebelow', ref_at=(124.46, ry - 8.89, 'left'), val_at=(124.46, ry + 8.89, 'left'))
    sh.wire(sh.N('R_RXIN', 'RXB_IN'), sh.P('R_RXPD', 1), sh.P(B, 2))
    sh.label((100.33, ry), 'RXB_IN')
    sh.sup(sh.P(B, 5), '+3V3')
    sh.gnd(sh.P(B, 3))
    sh.nc(sh.P(B, 1))
    sh.wire(sh.P(B, 4), (col, ry))
    sh.hlabel(Pt(col, ry), 'LINK_RX', 'R', 'output')
    sh.place('C_RXBUF', 99.06, ry - 11.43)
    sh.sup(sh.P('C_RXBUF', 1), '+3V3')
    sh.gnd(sh.P('C_RXBUF', 2))
    # TX: LINK_TX (100k down) -> buffer on CART_VCC -> 100R -> pin 31
    q = sh.P(J, 31)
    ty2 = Y
    sh.wire(q, (78.74, q[1]), (78.74, ty2), (82.55, ty2))
    tap_tp(sh, 'TP_PRX', (81.28, ty2), up=False)
    sh.label((q[0] + 1.27, q[1]), 'POCKET_RX')
    sh.place('R_TXOUT', 86.36, ty2, rot=90, fields='above')
    T = 'U_TXBUF'
    sh.place(T, 114.3, ty2, mirror='y', fields='abovebelow', ref_at=(104.14, ty2 - 8.89, 'right'),
             val_at=(104.14, ty2 + 8.89, 'right'))
    sh.wire(sh.N('R_TXOUT', 'TXB_OUT'), sh.P(T, 4))
    sh.label((93.98, ty2), 'TXB_OUT')
    sh.gnd(sh.P(T, 3))
    sh.nc(sh.P(T, 1))
    vc = sh.P(T, 5)
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    sh.place('R_TXPD', 139.7, ty2 + 3.81, fields='right')
    sh.gnd(sh.P('R_TXPD', 2))
    sh.wire((col, ty2), sh.P('R_TXPD', 1), sh.P(T, 2))
    sh.hlabel(Pt(col, ty2), 'LINK_TX', 'R', 'input')
    sh.text((30.48, 160.02),
            'The Pocket\'s slot: pin 1 the cart rail (3.3 V with the Pocket on), 5 the core\'s TX (GBA /CS), 31 its RX\n'
            '(GBA /REQ), 32 ground; the rest left open, as Analogue\'s template leaves them.  Both buffers are LVC with\n'
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    en = sh.P(U, 3)
    ey = en[1] - 17.78
    sh.wire(en, (X - 20.32, en[1]), (X - 20.32, ey), (X - 27.94, ey), (X - 38.1, ey), (X - 48.26, ey), (lcol, ey))
    sh.hlabel(Pt(lcol, ey), 'S3_EN', 'L', 'bidirectional')
    sh.place('R_EN', X - 27.94, ey - 3.81, fields='right')
    sh.sup(sh.P('R_EN', 1), '+3V3')
    sh.place('C_EN', X - 38.1, ey + 3.81, fields='right')
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    # IO0 (BOOT): button + the auto-program transistor
    io0 = sh.P(U, 27)
    sh.wire(io0, (X - 43.18, io0[1]), (lcol, io0[1]))
    sh.hlabel(Pt(lcol, io0[1]), 'S3_IO0', 'L', 'bidirectional')
    sh.place('SW_S3BOOT', X - 43.18, io0[1] + 5.08, rot=270, fields='left')
    sh.gnd(sh.P('SW_S3BOOT', 2))
    # WiFi (IO14, jogged up to its own row) and bus (IO16) LEDs, active low: +3V3 -> 1k -> LED -> GPIO
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    sh.wire(sh.N(R, 'SD_DAT1'), sh.N(J, 'SD_DAT1'))
    p, q = sh.N(R, 'SD_DAT2'), sh.N(J, 'SD_DAT2')
    sh.wire(p, (X + 50.8, p[1]), (X + 50.8, q[1]), q)
    sh.label((X + 53.34, sh.N(J, 'SD_DAT1')[1]), 'SD_DAT1')
    sh.label((X + 53.34, q[1]), 'SD_DAT2')
    for n in ('SD_CS', 'SD_MISO'):
        e = sh.stub(sh.N(R, n), 2.54)
        sh.label(e, n, 'R')
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    sh.place('R_SDCD', X + 104.14, Y + 38.1, fields='right')
    sh.sup(sh.P('R_SDCD', 1), '+3V3')
    e = sh.stub(sh.P('R_SDCD', 2))
    sh.label(e, 'SD_CD', 'D')
    sh.sup(sh.N(J, '+3V3'), '+3V3', n=2.54, rot=90)
    sh.gnd(sh.P(J, 6), n=2.54, rot=270)
    shp = [sh.P(J, n) for n in (10, 11, 12, 13)]
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    sh.gnd(sh.P('D_ESDM', 2), rot=180)
    sh.place('D_ESDP', 99.06, dp[0][1] + 3.81, rot=270, fields='right')
    sh.gnd(sh.P('D_ESDP', 2))
    sh.label((139.7, dm[0][1]), 'UBRG_DM')
    sh.label((139.7, dp[0][1]), 'UBRG_DP')
    for p in (sh.P(J, 'A8'), sh.P(J, 'B8')):
        sh.nc(p)
    g1, g2 = sh.P(J, 'A1'), sh.P(J, 'SH')
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    sh.place('R_VBSL', 144.78, sns[1] - 3.81, rot=180, fields='right')
    sh.wire(sh.P('R_VBSH', 2), (134.62, sns[1]), sh.P('R_VBSL', 1), sns)
    sh.gnd(sh.P('R_VBSL', 2), rot=180)
    sh.label((149.86, sns[1]), 'VBUS_SNS')
    vd, vr = sh.P(U, 6), sh.P(U, 7)
    top = 116.84
    sh.wire(vr, (vr[0], top))
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    sh.place('R_CPRST', 165.1, rst[1] - 3.81, fields='left')
    sh.wire(rst, (165.1, rst[1]))
    sh.sup(sh.P('R_CPRST', 1), '+3V3')
    sh.label((166.37, rst[1]), 'CP_RST')
    sh.gnd(sh.P(U, 3))
    sh.gnd(sh.P(U, 23), 2.54, rot=90)                      # /CTS tied low
    ncs(sh, U)
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    sh.wire((231.14, e1[1] + 5.08), (e1[0], e1[1] + 5.08), e1)
    sh.wire(dtr, (226.06, dtr[1]), (226.06, b1[1]), b1)
    sh.wire((226.06, b1[1]), (226.06, e2[1] + 5.08), (e2[0], e2[1] + 5.08), e2)
    sh.label((215.9, rts[1]), 'UART_RTS')
    sh.label((215.9, dtr[1]), 'UART_DTR')
    for c, n in ((c1, 'S3_EN'), (c2, 'S3_IO0')):
        sh.wire(c, (c[0], c[1] - 2.54), (rcol, c[1] - 2.54))
        sh.hlabel(Pt(rcol, c[1] - 2.54), n, 'R', 'output')
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    st = sh.P(U, 1)
    sh.place('D_CHG', 91.44, st[1], fields='below')
    sh.wire(st, sh.N('D_CHG', 'CHG_STAT'))
    sh.label((73.66, st[1]), 'CHG_STAT')
    sh.place('R_CHGLED', 104.14, st[1], rot=270, fields='below')
    sh.wire(sh.N('D_CHG', 'CHG_LED_A'), sh.N('R_CHGLED', 'CHG_LED_A'))
    sh.name((97.79, st[1]), 'CHG_LED_A', 'U', 'L')
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    sh.sup(sh.P(E, 2), 'VBUS', rot=270)
    a1 = sh.P(E, 1)
    sh.wire(a1, (33.02, a1[1]))
    sh.hlabel(Pt(33.02, a1[1]), 'CART_VCC', 'L', 'input')
    # PWR_FLAGs: GND and VBUS reach the board only through connector (passive) pins
    sh.wire((25.4, 134.62), (35.56, 134.62))
    sh.gnd((25.4, 134.62))
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        sh.label((es[n][0] + 3.81, es[n][1]), n)
    c = ep['CART_VCC']
    sh.wire(c, (99.06, c[1]), (99.06, pw['CART_VCC'][1]), pw['CART_VCC'])
    sh.label((c[0] + 3.81, c[1]), 'CART_VCC')
    sh.text((30.48, 139.7), NOTES, 1.524)
    return sh

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
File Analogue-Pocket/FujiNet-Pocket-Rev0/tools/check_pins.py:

#!/usr/bin/env python3
"""The schematic against the firmware: design.py's ESP32-S3 nets against firmware/pocket.h (the pin
map this board proposes for fujinet-firmware), and the link path against what the openFPGA-7800
core expects on the Pocket's slot (pin 5 its TX, pin 31 its RX, pin 1 the rail).

Checks, each a hard failure:
  * every GPIO pocket.h names (UART0, UART1, SD, LEDs) is on the S3 pad design.py wires to that
    function's net, and no other pad carries that net;
  * no used GPIO is a strapping pin (0, 3, 45, 46 -- IO0 only as BOOT) or the N16R8's octal
    PSRAM (35-37);
  * slot pin 5 -> 100R -> the RX buffer's input; its output is UART1 RX; the RX buffer runs on +3V3;
  * UART1 TX -> the TX buffer's input; its output -> 100R -> slot pin 31; the TX buffer runs on the
    slot's rail (pin 1) and nothing else on that rail but its decoupling, the enable diode and pads.

Usage: python3 tools/check_pins.py
"""
import os, re, sys
sys.path.insert(0, os.path.dirname(os.path.abspath(__file__)))
import design as D

HERE = os.path.dirname(os.path.abspath(__file__))
H = os.path.join(HERE, '..', 'firmware', 'pocket.h')

# pocket.h define -> the design.py net on that GPIO
WANT = {'PIN_UART0_RX': 'S3_RXD', 'PIN_UART0_TX': 'S3_TXD',
        'PIN_UART1_RX': 'LINK_RX', 'PIN_UART1_TX': 'LINK_TX',
        'PIN_SD_HOST_CS': 'SD_CS', 'PIN_SD_HOST_SCK': 'SD_SCK', 'PIN_SD_HOST_MISO': 'SD_MISO',
        'PIN_SD_HOST_MOSI': 'SD_MOSI', 'PIN_LED_WIFI': 'LED_WIFI', 'PIN_LED_BUS': 'LED_BUS'}
NC_REQUIRED = ['PIN_BUTTON_A', 'PIN_BUTTON_B', 'PIN_BUTTON_C', 'PIN_LED_BT', 'PIN_RS232_RTS', 'PIN_RS232_CTS',
               'PIN_RS232_DTR', 'PIN_RS232_DSR', 'PIN_RS232_DCD', 'PIN_RS232_RI']
STRAP, PSRAM = {3, 45, 46}, {35, 36, 37}
# the module's UART0 pads carry their own names in the symbol
PAD_GPIO = {'RXD0': 44, 'TXD0': 43}

bad = []


def fail(msg):
    bad.append(msg)


def main():
    src = open(H).read()
    defs = dict(re.findall(r'#define\s+(PIN_\w+)\s+(GPIO_NUM_\w+|UART_NUM_\d)', src))
    s3 = D.BY_KEY['U_S3']
    pad_fn = {}
    for fn, pad in D.S3_PAD.items():
        for p in (pad if isinstance(pad, list) else [pad]):
            pad_fn[str(p)] = fn
    gpio_net = {}
    for pad, net in s3.pins.items():
        fn = pad_fn[pad]
        g = PAD_GPIO.get(fn) if fn in PAD_GPIO else (int(fn[2:]) if fn.startswith('IO') else None)
        if g is not None:
            gpio_net[g] = net
    for name, net in WANT.items():
        v = defs.get(name)
        if not v or v == 'GPIO_NUM_NC':
            fail('%s missing or NC in pocket.h' % name)
            continue
        g = int(v.split('_')[-1])
        if gpio_net.get(g) != net:
            fail('%s = GPIO%d, but the schematic puts %s there (want %s)' % (name, g, gpio_net.get(g), net))
        others = [x for x, n in gpio_net.items() if n == net and x != g]
        if others:
            fail('%s also on GPIO %s' % (net, others))
        if g in STRAP or g in PSRAM:
            fail('%s = GPIO%d: a strapping / PSRAM pin' % (name, g))
    for name in NC_REQUIRED:
        if defs.get(name) != 'GPIO_NUM_NC':
            fail('%s must be GPIO_NUM_NC (got %s)' % (name, defs.get(name)))
    if defs.get('PIN_BUS_UART') != 'UART_NUM_1':
        fail('PIN_BUS_UART must be UART_NUM_1')
    for g, net in gpio_net.items():
        if net and (g in STRAP or g in PSRAM):
            fail('GPIO%d (strapping / PSRAM) carries %s' % (g, net))
    if gpio_net.get(0) != 'S3_IO0':
        fail('GPIO0 must be the BOOT net only')

    # the link path, part by part
    E = D.BY_KEY['J_EDGE'].pins
    if (E['1'], E['5'], E['31'], E['32']) != ('CART_VCC', 'POCKET_TX', 'POCKET_RX', 'GND'):
        fail('slot pins 1 / 5 / 31 / 32: %s' % [E[k] for k in ('1', '5', '31', '32')])
    if [n for k, n in E.items() if k not in ('1', '5', '31', '32') and n]:
        fail('slot pins other than 1, 5, 31, 32 are connected')
    rx, tx = D.BY_KEY['U_RXBUF'].pins, D.BY_KEY['U_TXBUF'].pins
    rin, rout = D.BY_KEY['R_RXIN'].pins, D.BY_KEY['R_TXOUT'].pins
    if set(rin.values()) != {'POCKET_TX', rx['2']}:
        fail('pin 5 does not reach the RX buffer through R_RXIN')
    if rx['4'] != 'LINK_RX' or rx['5'] != '+3V3':
        fail('RX buffer: Y %s, VCC %s' % (rx['4'], rx['5']))
    if tx['2'] != 'LINK_TX' or tx['5'] != 'CART_VCC':
        fail('TX buffer: A %s, VCC %s' % (tx['2'], tx['5']))
    if set(rout.values()) != {'POCKET_RX', tx['4']}:
        fail('the TX buffer does not reach pin 31 through R_TXOUT')
    on_rail = sorted(p.key for p in D.PARTS if 'CART_VCC' in p.pins.values())
    if on_rail != sorted(['J_EDGE', 'U_TXBUF', 'C_TXBUF', 'TP_CVCC', 'D_EN']):
        fail('CART_VCC (the Pocket\'s rail) feeds %s' % on_rail)

    if bad:
        raise SystemExit('check_pins:\n  ' + '\n  '.join(bad))
    print('check_pins: pocket.h and the link path match the schematic (%d GPIOs)' % len(WANT))


if __name__ == '__main__':
    main()

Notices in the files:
Analogue-Pocket/FujiNet-Pocket-Rev0/README.md:
Provenance and license:
- **Symbols and footprints:** official KiCad libraries (CC-BY-SA 4.0 with exception), except the
project's own (the Pocket edge; the T
Analogue-Pocket/FujiNet-Pocket-Rev0/FujiNet-Pocket-Rev0.kicad_pcb:
CERN-OHL-W-2.0  FujiNet Pocket Rev0
Analogue-Pocket/FujiNet-Pocket-Rev0/FujiNet-Pocket-Rev0.kicad_sch:
CERN-OHL-W-2.0 (derived from FujiNet-7800-Rev0 and its sources)
FujiNet half: FujiNet-7800-Rev0 (fujinet-hardware, CERN-OHL-W-2.0).  Edge geometry: Gekkio GB-CART32K-A (CC-BY-4.0).
